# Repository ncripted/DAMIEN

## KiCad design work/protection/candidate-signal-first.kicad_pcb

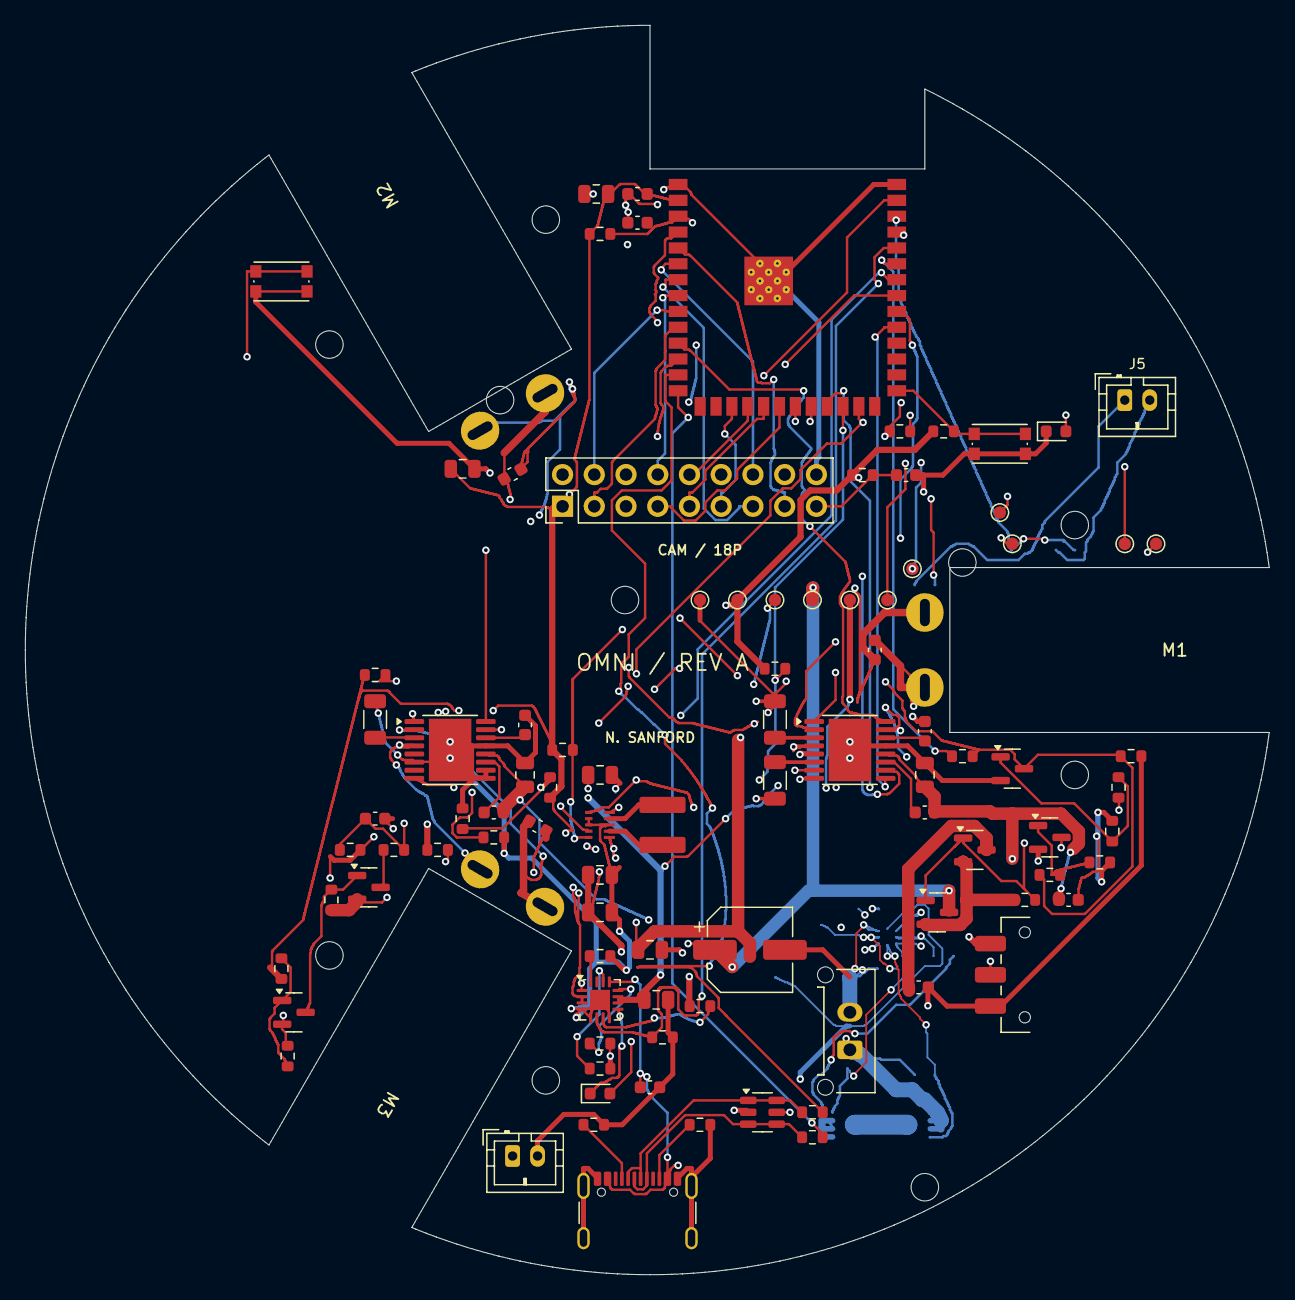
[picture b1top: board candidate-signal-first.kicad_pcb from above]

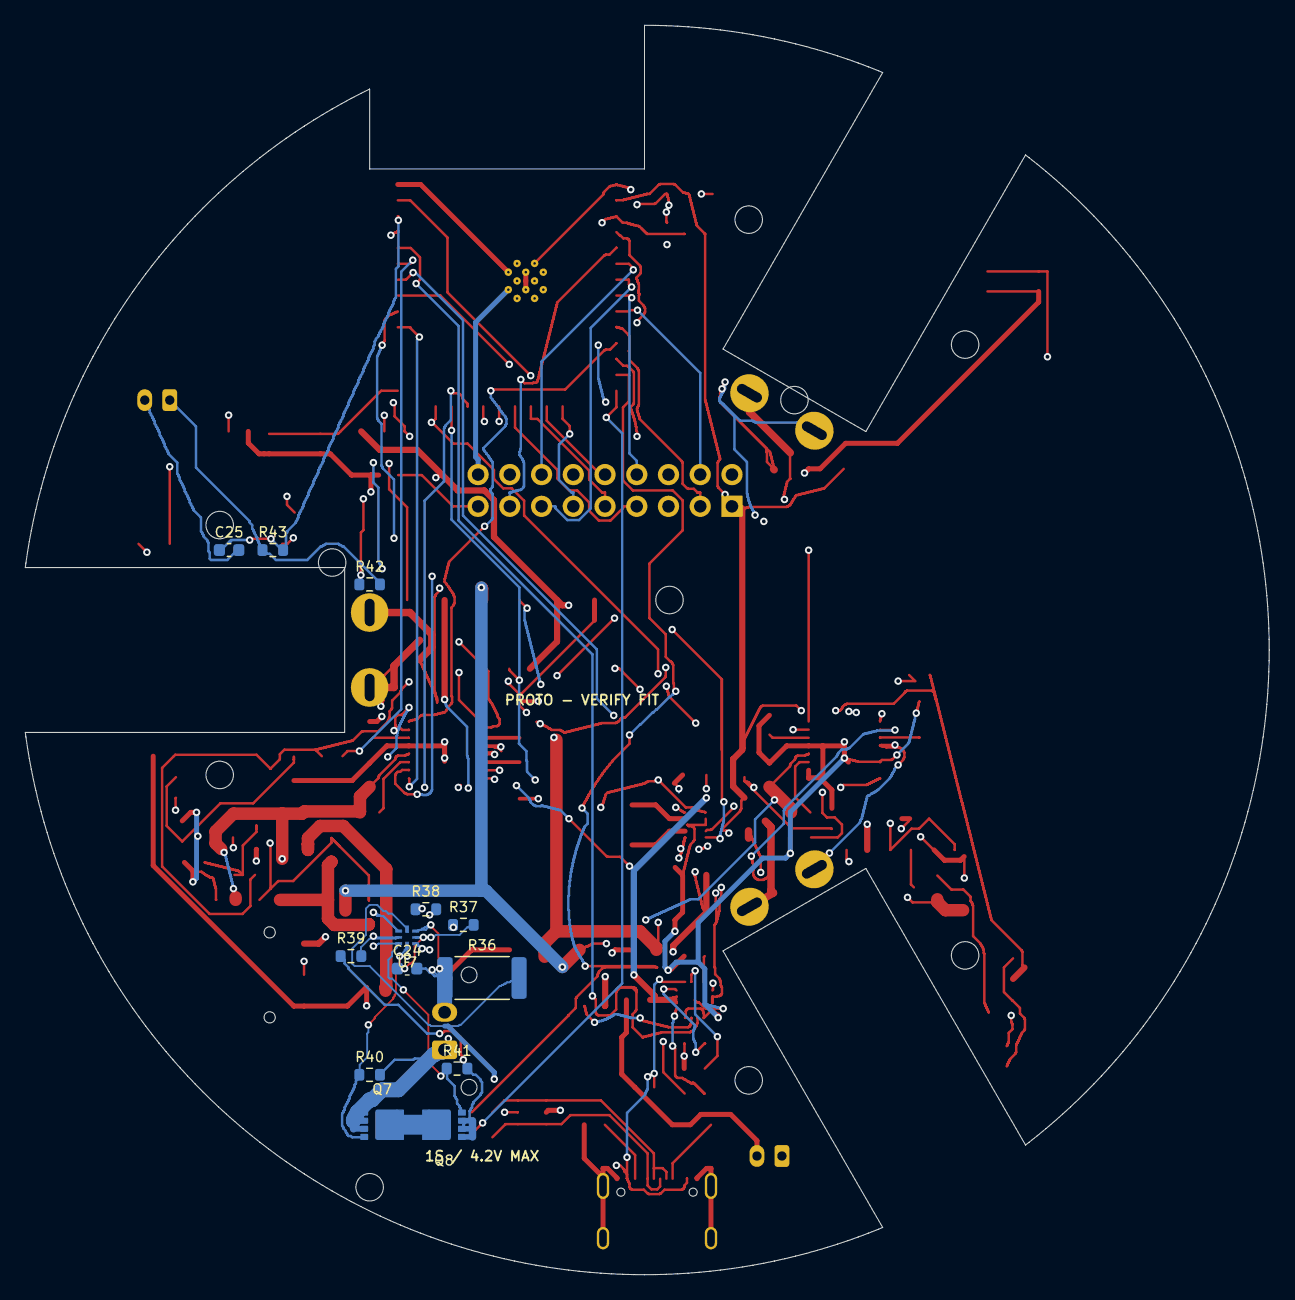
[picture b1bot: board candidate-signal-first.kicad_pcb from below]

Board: 4 copper layers, 99.6 x 100.0 mm, 119 parts (13 on the bottom side), 85 nets.

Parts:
C1, C15, C21: 1u/10V; Capacitor_SMD__C_0603_1608Metric
C2, C5, C6, C9, C16, C17, C18: 10u/10V; Capacitor_SMD__C_0805_2012Metric
C3, C4, C22, C23: 100n/16V; Capacitor_SMD__C_0603_1608Metric
C7, C10: 2.2u/10V; Capacitor_SMD__C_0603_1608Metric
C8, C11: 10n/25V; Capacitor_SMD__C_0603_1608Metric
C12, C13, C14: 100n/25V; Capacitor_SMD__C_0603_1608Metric
C19, C20: 22u/10V; Capacitor_SMD__C_0805_2012Metric
C24, C25: 100n/16V X7R; Capacitor_SMD__C_0603_1608Metric
C90: 220u/10V; CP_Elec_6.3x5.8_HandAssembly
D1: STATUS GREEN; LED_SMD__LED_0603_1608Metric
D2: CHARGE AMBER; LED_SMD__LED_0603_1608Metric
H1, H2, H3, H4, H5, H6, H7, H8, H9, H10: M2; MountingHole_2.2mm_M2
J1: USB-C; Connector_USB__USB_C_Receptacle_GCT_USB4105-xx-A_16P_TopMnt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
J2: RAW 1S CELL 4.2V MAX; Connector_Molex__Molex_Micro-Fit_3.0_43650-0215_1x02_P3.00m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
J3: WAVESHARE OV2640 18P; Connector_PinHeader_2.54mm__PinHeader_2x09_P2.54mm_Vertical
J4: CELL NTC - CHARGER; Connector_JST__JST_PH_B2B-PH-K_1x02_P2.00mm_Vertical
J5: CELL NTC - DRIVE; Connector_JST__JST_PH_B2B-PH-K_1x02_P2.00mm_Vertical
L1: 0.47uH/5.4A; L_XFL4015
M1: POLOLU 3065 MOTOR 1; Pololu_HPCB_Solder
M2: POLOLU 3065 MOTOR 2; Pololu_HPCB_Solder
M3: POLOLU 3065 MOTOR 3; Pololu_HPCB_Solder
Q1, Q2, Q5: AO3401A; Package_TO_SOT_SMD__SOT-23
Q3, Q4, Q6: MMBT3904; Package_TO_SOT_SMD__SOT-23
Q7, Q8: CSD17308Q3; CSD17308Q3_TI
R1, R2, R4, R5, R8, R29: 10k; Resistor_SMD__R_0603_1608Metric
R3, R27: 1k; Resistor_SMD__R_0603_1608Metric
R6, R7, R9: 0.25R/0.5W; Resistor_SMD__R_1206_3216Metric
R10, R11: 5.1k; Resistor_SMD__R_0603_1608Metric
R12, R13: 22R; Resistor_SMD__R_0603_1608Metric
R14: 3.57k; Resistor_SMD__R_0603_1608Metric
R15: 3.24k; Resistor_SMD__R_0603_1608Metric
R16: 46.4k; Resistor_SMD__R_0603_1608Metric
R17, R19, R22, R23, R24, R25, R26, R28, R30, R31, R33, R34, R35: 100k; Resistor_SMD__R_0603_1608Metric
R18: 2.2k; Resistor_SMD__R_0603_1608Metric
R20: 511k; Resistor_SMD__R_0603_1608Metric
R21: 91k; Resistor_SMD__R_0603_1608Metric
R32: 47k; Resistor_SMD__R_0603_1608Metric
R36: 10m 1% 1W; Resistor_SMD__R_2512_6332Metric
R37: 100R 1%; Resistor_SMD__R_0603_1608Metric
R38: 20R 1%; Resistor_SMD__R_0603_1608Metric
R39, R43: 1k 1%; Resistor_SMD__R_0603_1608Metric
R40, R41: 10M; Resistor_SMD__R_0603_1608Metric
R42: 10k 1%; Resistor_SMD__R_0603_1608Metric
SW1: RESET; Button_Switch_SMD__SW_Push_1P1T_NO_CK_KMR2
SW2: BOOT; Button_Switch_SMD__SW_Push_1P1T_NO_CK_KMR2
SW3: POWER; Button_Switch_SMD__SW_SPDT_CK_JS102011SAQN
TP1: GND; TestPoint__TestPoint_Pad_D1.0mm
TP2: +3V3; TestPoint__TestPoint_Pad_D1.0mm
TP3: VBAT; TestPoint__TestPoint_Pad_D1.0mm
TP4: VMOTOR; TestPoint__TestPoint_Pad_D1.0mm
TP5: SYS_RAW; TestPoint__TestPoint_Pad_D1.0mm
TP6: ESP_EN; TestPoint__TestPoint_Pad_D1.0mm
TP7: LED_STATUS; TestPoint__TestPoint_Pad_D1.0mm
TP8: DRIVE_ENABLE; TestPoint__TestPoint_Pad_D1.0mm
TP9: FAULT_U2; TestPoint__TestPoint_Pad_D1.0mm
TP10: FAULT_U3; TestPoint__TestPoint_Pad_D1.0mm
TP11: REG_PG; TestPoint__TestPoint_Pad_D1.0mm
U1: ESP32-S3-WROOM-1-N8R8; RF_Module__ESP32-S3-WROOM-1
U2, U3: DRV8833PWP; Package_SO__HTSSOP-16-1EP_4.4x5mm_P0.65mm_EP3.4x5mm_Mask2.4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
U4: TPS63802DLA; TPS63802_DLA0010A
U5: BQ24074RGT; Package_DFN_QFN__VQFN-16-1EP_3x3mm_P0.5mm_EP1.6x1.6mm
U6: USBLC6-2SC6; Package_TO_SOT_SMD__SOT-23-6
U7: BQ298217RUGR; BQ298217_RUG0008A

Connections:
+3V3: C2.1, C3.1, C5.1, C19.1, C20.1, J3.1, R1.1, R2.1, R4.1, R5.1, R8.1, R19.1, R20.1, R22.1, R32.1, R42.1, TP2.1, U1.2, U4.6
BAT_NTC: J4.1, U5.1
CAM_D0: J3.16, U1.4
CAM_D1: J3.15, U1.5
CAM_D2: J3.14, U1.6
CAM_D3: J3.13, U1.7
CAM_D4: J3.12, U1.12
CAM_D5: J3.11, U1.17
CAM_D6: J3.10, U1.18
CAM_D7: J3.9, U1.19
CAM_HREF: J3.6, U1.22
CAM_PCLK: J3.7, U1.20
CAM_RESET: C4.1, J3.17, R4.2
CAM_SCL: J3.3, U1.10
CAM_SDA: J3.4, U1.9
CAM_VSYNC: J3.5, U1.21
CAM_XCLK: J3.8, U1.8
CELL_N: C24.2, J2.2, R36.1, U7.3, U7.5
CELL_P: J2.1, Q7.1, Q7.2, Q7.3, R37.1, R38.1, R40.2
CELL_TEMP_ADC: C25.1, R43.2, U1.38
CELL_TEMP_DIV: J5.1, R42.2, R43.1
CHG_ILIM: R15.1, U5.12
CHG_ISET: R14.1, U5.16
CHG_LED_A: D2.2, R18.2
CHG_PGOOD: R19.2, U5.7
CHG_STATUS: D2.1, U5.9
CHG_TIMER: R16.1, U5.14
DRIVE_ENABLE: Q4.3, R25.1, R27.2, R28.1, TP8.1, U2.1, U3.1
DRIVE_REQ: R27.1, U1.35
ESP_BOOT: R2.2, SW2.1, U1.27
ESP_EN: C1.1, R1.2, SW1.1, TP6.1, U1.3
FAULT_U2: R5.2, TP9.1, U1.24, U2.8
FAULT_U3: R8.2, TP10.1, U1.25, U3.8
GND: C1.2, C2.2, C3.2, C4.2, C5.2, C6.2, C7.2, C9.2, C10.2, C15.2, C16.2, C17.2, C18.2, C19.2, C20.2, C21.2, C22.2, C23.2, C25.2, C90.2, D1.1, J1.A1, J1.A12, J1.B1, J1.B12, J1.S1, J3.2, J3.18, J4.2, J5.2, Q3.2, Q4.2, Q6.2, R6.2, R7.2, R9.2, R10.2, R11.2, R14.2, R15.2, R16.2, R17.2, R21.2, R23.2, R26.2, R28.2, R30.2, R33.2, R35.2, R36.2, SW1.2, SW2.2, SW3.1, TP1.1, U1.1, U1.40, U1.41, U2.13, U2.17, U3.6, U3.9, U3.10, U3.13, U3.17, U4.2, U4.3, U4.8, U5.4, U5.5, U5.8, U5.17, U6.2, U7.4
LED_A: D1.2, R3.2
LED_STATUS: R3.1, TP7.1, U1.37
M1_A: C12.1, M1.1, U2.2
M1_B: C12.2, M1.2, U2.4
M1_IN1: U1.11, U2.16
M1_IN2: U1.23, U2.15
M1_SENSE: R6.1, U2.3
M2_A: C13.1, M2.1, U2.7
M2_B: C13.2, M2.2, U2.5
M2_IN1: U1.31, U2.9
M2_IN2: U1.32, U2.10
M2_SENSE: R7.1, U2.6
M3_A: C14.1, M3.1, U3.2
M3_B: C14.2, M3.2, U3.4
M3_IN1: U1.33, U3.16
M3_IN2: U1.34, U3.15
M3_SENSE: R9.1, U3.3
MEAS_BASE: Q6.1, R32.2, R33.1
MEAS_GATE: Q5.1, Q6.3, R31.2
MOTOR_BASE: Q3.1, R25.2, R26.1
MOTOR_GATE: Q1.1, Q2.1, Q3.3, R24.2
MOTOR_MID: Q1.2, Q2.2, R24.1
PROT_BAT: R38.2, U7.1
PROT_CHG: Q7.4, R40.1, U7.8
PROT_DRAIN: Q7.5, Q7.6, Q7.7, Q7.8, Q7.9, Q8.5, Q8.6, Q8.7, Q8.8, Q8.9
PROT_DSG: Q8.4, R41.1, U7.7
PROT_PACK: R39.2, U7.6
PROT_VDD: C24.1, R37.2, U7.2
REG_FB: R20.2, R21.1, U4.4
REG_L1: L1.1, U4.9
REG_L2: L1.2, U4.7
REG_PG: R22.2, TP11.1, U4.5
SYS_ON: R23.1, SW3.2, U4.1
SYS_RAW: C17.1, C18.1, R18.1, SW3.3, TP5.1, U4.10, U5.10, U5.11
U2_VCP: C8.1, U2.11
U2_VINT: C7.1, U2.14
U3_VCP: C11.1, U3.11
U3_VINT: C10.1, U3.14
USB_5V: C15.1, J1.A4, J1.A9, J1.B4, J1.B9, R29.1, U5.13, U6.5
USB_500_ENABLE: R17.1, U1.36, U5.6
USB_CC1: J1.A5, R10.1
USB_CC2: J1.B5, R11.1
USB_DETECT_BASE: Q4.1, R29.2, R30.1
USB_DM: R12.2, U1.13
USB_DM_EXT: J1.A7, J1.B7, R12.1, U6.1, U6.6
USB_DP: R13.2, U1.14
USB_DP_EXT: J1.A6, J1.B6, R13.1, U6.3, U6.4
VBAT: C16.1, C21.1, Q1.3, Q5.2, Q8.1, Q8.2, Q8.3, R31.1, R39.1, R41.2, TP3.1, U5.2, U5.3
VBAT_ADC: C23.1, R34.2, R35.1, U1.39
VBAT_MEAS: Q5.3, R34.1
VMOTOR: C6.1, C8.2, C9.1, C11.2, C22.1, C90.1, Q2.3, TP4.1, U2.12, U3.12
